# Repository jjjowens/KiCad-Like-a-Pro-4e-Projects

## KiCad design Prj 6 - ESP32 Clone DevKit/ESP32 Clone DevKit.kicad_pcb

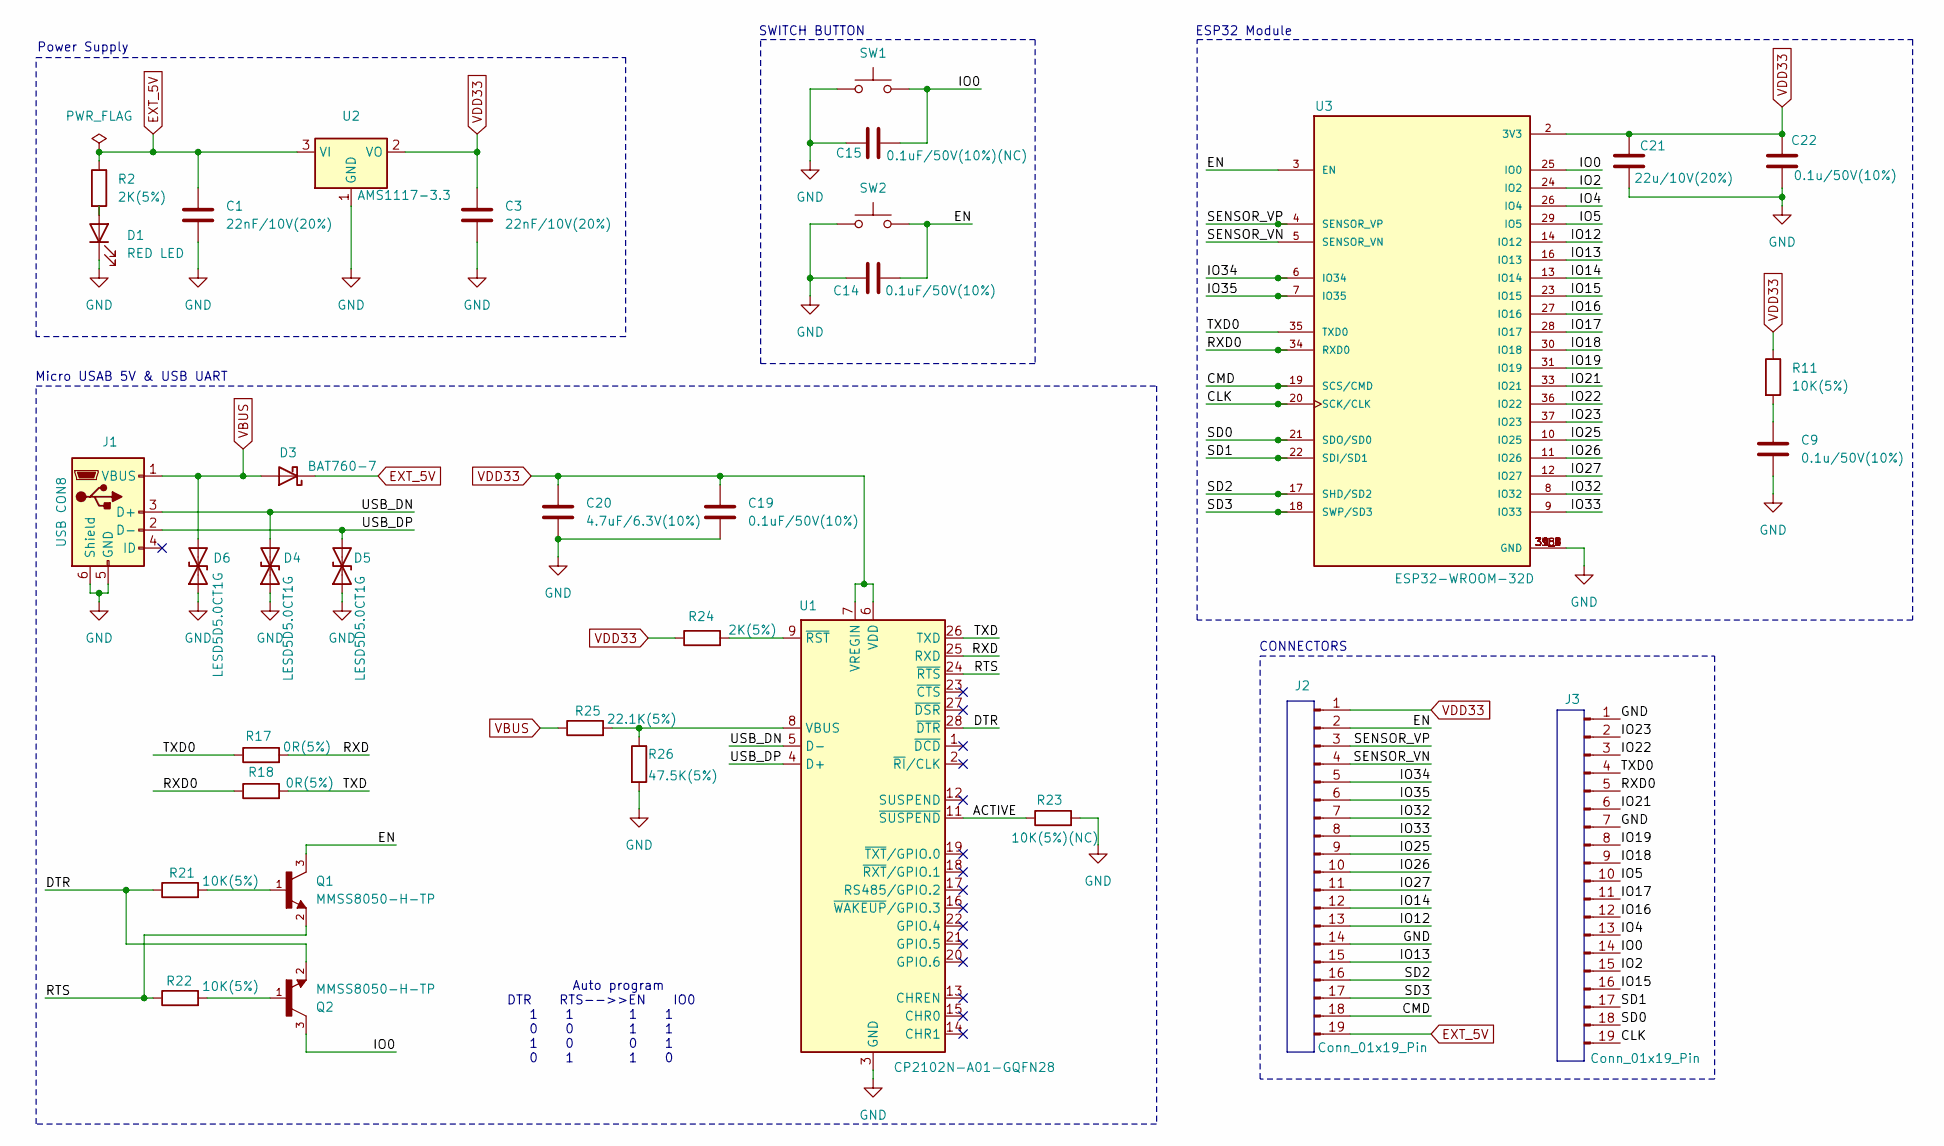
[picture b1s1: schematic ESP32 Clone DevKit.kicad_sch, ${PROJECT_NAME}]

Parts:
C1, C3: 22nF/10V(20%); C_0201_0603Metric
C9, C22: 0.1u/50V(10%); C_01005_0402Metric
C14, C19: 0.1uF/50V(10%); C_01005_0402Metric
C15: 0.1uF/50V(10%)(NC); C_01005_0402Metric
C20: 4.7uF/6.3V(10%); C_01005_0402Metric
C21: 22u/10V(20%); C_0201_0603Metric
D1: RED LED; LED_0603_1608Metric
D3: BAT760-7; D_SOD-323
D4, D5, D6: LESD5D5.0CT1G; D_SOD-523
J1: USB CON8; USB_Micro-AB_Molex_47590-0001
J2, J3: Conn_01x19_Pin; PinHeader_1x19_P2.54mm_Vertical
Q1, Q2: MMSS8050-H-TP; TRANS_MMSS8050-H-TP; PARTREV D
R2, R24: 2K(5%); R_01005_0402Metric_Pad0.57x0.30mm_HandSolder
R11, R21, R22: 10K(5%); R_01005_0402Metric_Pad0.57x0.30mm_HandSolder
R17, R18: 0R(5%); R_01005_0402Metric_Pad0.57x0.30mm_HandSolder
R23: 10K(5%)(NC); R_01005_0402Metric_Pad0.57x0.30mm_HandSolder
R25: 22.1K(5%); R_01005_0402Metric_Pad0.57x0.30mm_HandSolder
R26: 47.5K(5%); R_01005_0402Metric_Pad0.57x0.30mm_HandSolder
SW1, SW2: SW_Push; SW_SPST_B3S-1000
U1: CP2102N-A01-GQFN28; QFN-28-1EP_5x5mm_P0.5mm_EP3.35x3.35mm
U2: AMS1117-3.3; SOT-223-3_TabPin2
U3: ESP32-WROOM-32D; MODULE_ESP32-WROOM-32D; PARTREV 1.9

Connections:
/ACTIVE: R23.1, U1.11 (~SUSPEND)
/CLK: J3.19, U3.20 (SCK/CLK)
/CMD: J2.18, U3.19 (SCS/CMD)
/DTR: Q2.2, R21.1, U1.28 (~DTR)
/EN: C14.2, J2.2, Q1.3, SW2.2, U3.3 (EN); also elsewhere on the board
/IO0: C15.2, J3.14, Q2.3, SW1.2, U3.25 (IO0); also elsewhere on the board
/IO2: J3.15, U3.24 (IO2)
/IO4: J3.13, U3.26 (IO4)
/IO5: J3.10, U3.29 (IO5)
/IO12: J2.13, U3.14 (IO12)
/IO13: J2.15, U3.16 (IO13)
/IO14: J2.12, U3.13 (IO14)
/IO15: J3.16, U3.23 (IO15)
/IO16: J3.12, U3.27 (IO16)
/IO17: J3.11, U3.28 (IO17)
/IO18: J3.9, U3.30 (IO18)
/IO19: J3.8, U3.31 (IO19)
/IO21: J3.6, U3.33 (IO21)
/IO22: J3.3, U3.36 (IO22)
/IO23: J3.2, U3.37 (IO23)
/IO25: J2.9, U3.10 (IO25)
/IO26: J2.10, U3.11 (IO26)
/IO27: J2.11, U3.12 (IO27)
/IO32: J2.7, U3.8 (IO32)
/IO33: J2.8, U3.9 (IO33)
/IO34: J2.5, U3.6 (IO34)
/IO35: J2.6, U3.7 (IO35)
/RTS: Q1.2, R22.1, U1.24 (~RTS)
/RXD: R17.2, U1.25 (RXD)
/RXD0: J3.5, R18.1, U3.34 (RXD0)
/SD0: J3.18, U3.21 (SDO/SD0)
/SD1: J3.17, U3.22 (SDI/SD1)
/SD2: J2.16, U3.17 (SHD/SD2)
/SD3: J2.17, U3.18 (SWP/SD3)
/SENSOR_VN: J2.4, U3.5 (SENSOR_VN)
/SENSOR_VP: J2.3, U3.4 (SENSOR_VP)
/TXD: R18.2, U1.26 (TXD)
/TXD0: J3.4, R17.1, U3.35 (TXD0)
/USB_DN: D4.2 (A2), J1.3 (D+), U1.5 (D-)
/USB_DP: D5.2 (A2), J1.2 (D-), U1.4 (D+)
EXT_5V: C1.1, D3.1 (K), J2.19, R2.1, U2.3 (VI)
GND: C1.2, C3.2, C9.2, C14.1, C15.1, C19.2, C20.2, C21.2, C22.2, D1.1 (K), D4.1 (A1), D5.1 (A1), D6.1 (A1), J1.5 (GND), J1.6 (Shield), J2.14, J3.1, J3.7, R23.2, R26.2, SW1.1, SW2.1, U1.3 (GND), U1.29 (GND), U2.1 (GND), U3.1 (GND), U3.15 (GND), U3.38 (GND), U3.39_1 (GND), U3.39_2 (GND), U3.39_3 (GND), U3.39_4 (GND), U3.39_5 (GND), U3.39_6 (GND), U3.39_7 (GND), U3.39_8 (GND), U3.39_9 (GND); also elsewhere on the board
unnamed: C9.1, R11.2
unnamed: D1.2 (A), R2.2
unnamed: Q1.1, R21.2
unnamed: Q2.1, R22.2
unnamed: R25.2, R26.1, U1.8 (VBUS)
unnamed: R24.2, U1.9 (~RST)
VBUS: D3.2 (A), D6.2 (A2), J1.1 (VBUS), R25.1
VDD33: C3.1, C19.1, C20.1, C21.1, C22.1, J2.1, R11.1, R24.1, U1.6 (VDD), U1.7 (VREGIN), U2.2 (VO), U3.2 (3V3)

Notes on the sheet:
CONNECTORS
SWITCH BUTTON
ESP32 Module
Micro USAB 5V & USB UART
Auto program DTR RTS-->>EN IO0 1 1 1 1 0 0 1 1 1 0 0 1 0 1 1 0
Power Supply

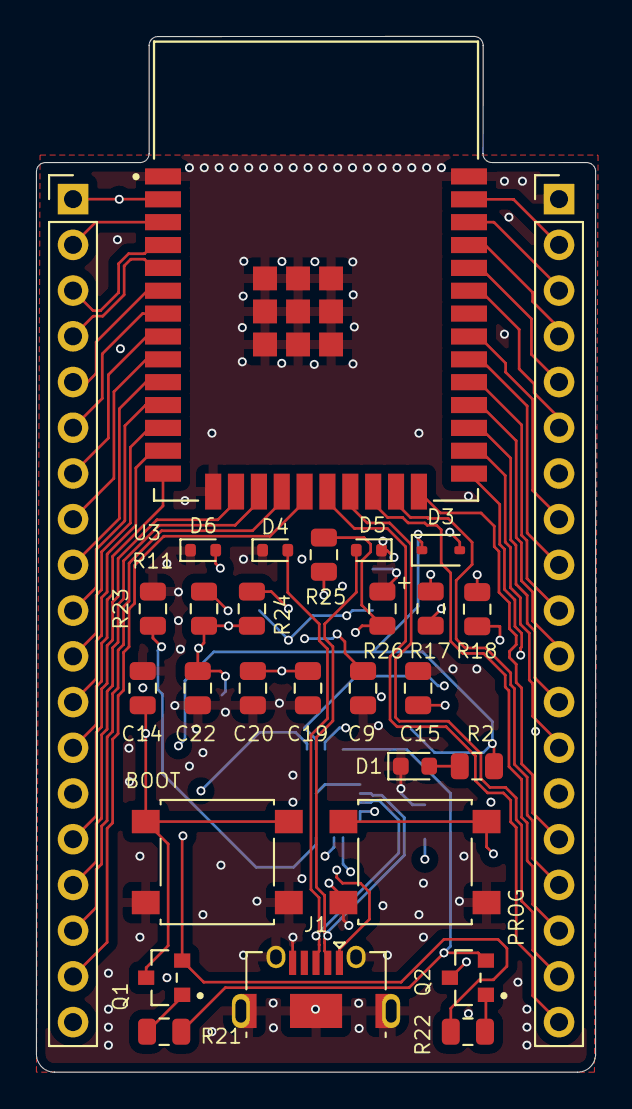
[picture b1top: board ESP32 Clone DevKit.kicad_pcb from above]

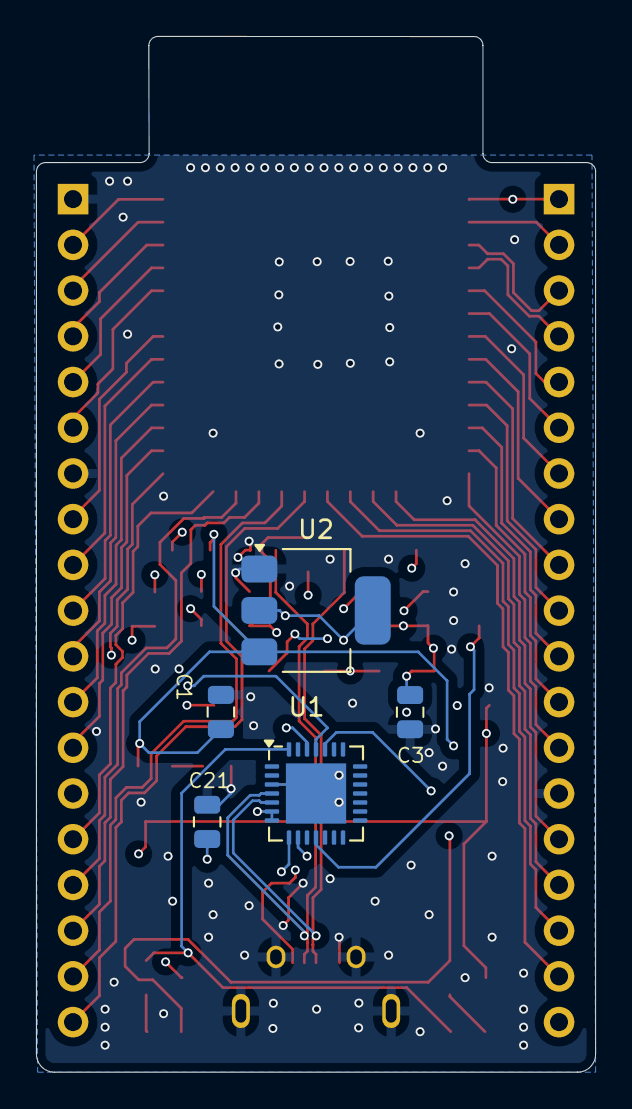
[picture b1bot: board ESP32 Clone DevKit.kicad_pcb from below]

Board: 4 copper layers, 31.1 x 57.5 mm, 34 parts (5 on the bottom side), 50 nets.

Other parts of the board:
BOOT: SW_Push; SW_SPST_B3S-1000
PROG: SW_Push; SW_SPST_B3S-1000

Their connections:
/EN: BOOT.2; also elsewhere on the board
/IO0: PROG.2; also elsewhere on the board
GND: BOOT.1, PROG.1; also elsewhere on the board

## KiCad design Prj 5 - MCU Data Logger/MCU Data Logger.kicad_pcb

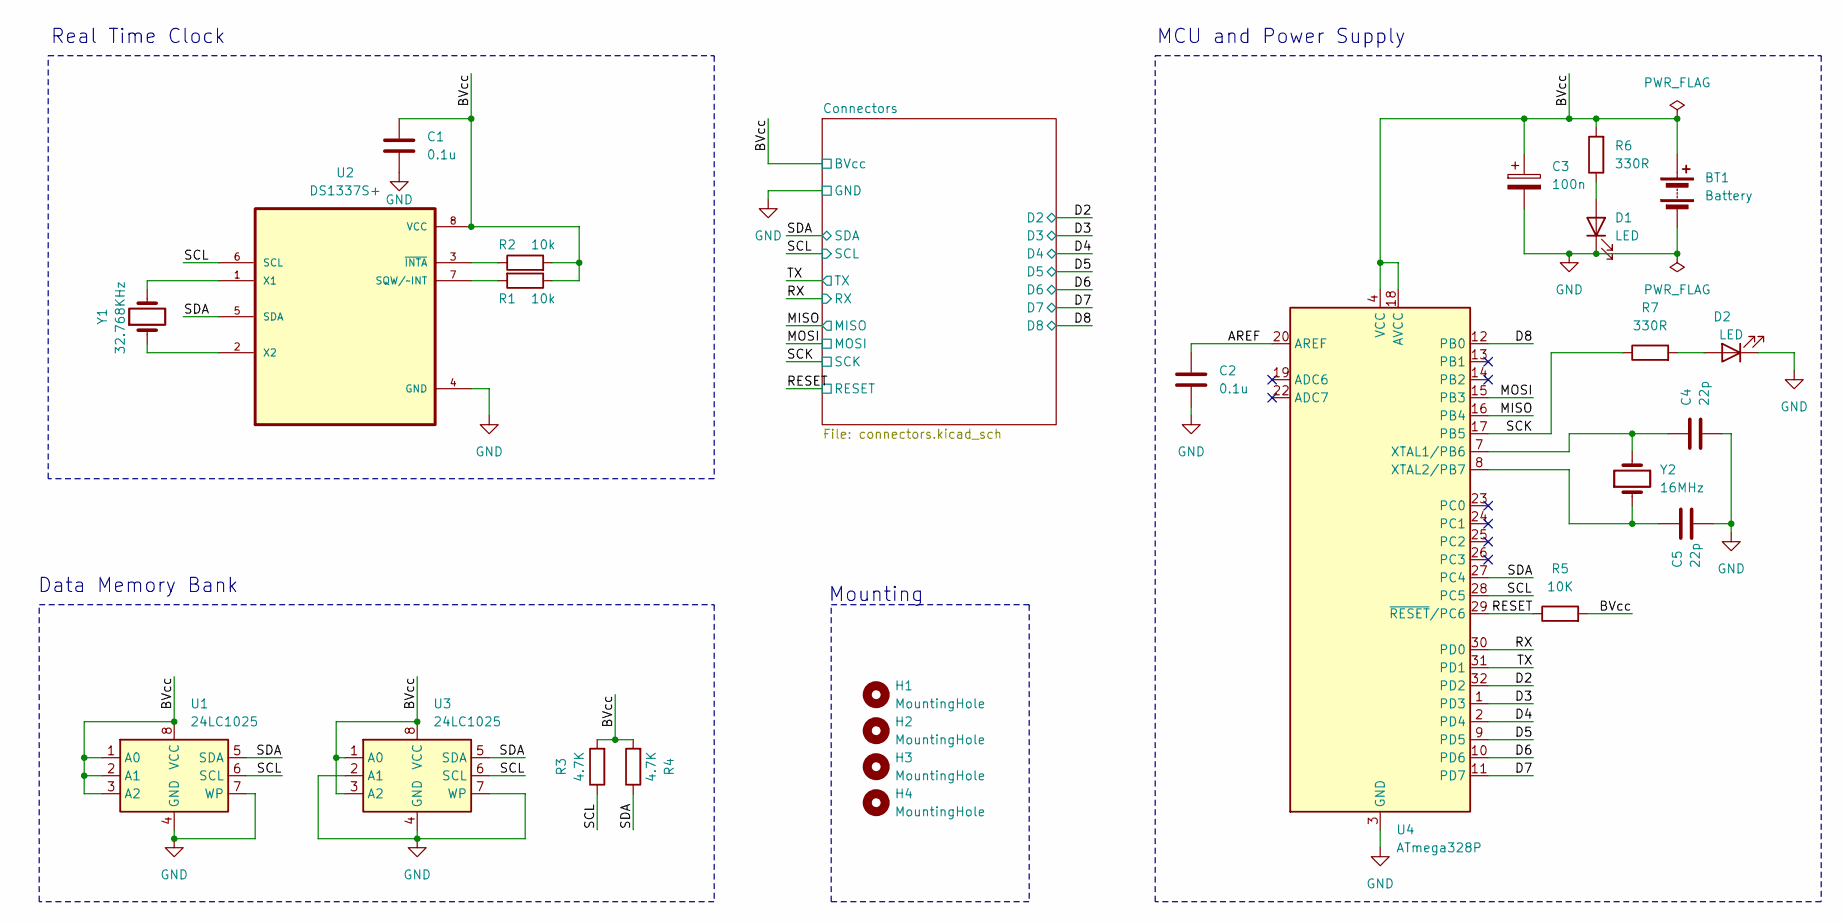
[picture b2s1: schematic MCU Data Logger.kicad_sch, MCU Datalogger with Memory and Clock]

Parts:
BT1: Battery; PinHeader_1x02_P2.54mm_Vertical
C1, C2: 0.1u; C_0805_2012Metric
C3: 100n; C_0805_2012Metric
C4, C5: 22p; C_0805_2012Metric
D1, D2: LED; LED_0805_2012Metric
H1, H2, H3, H4: MountingHole; MountingHole_2.1mm
R1, R2: 10k; R_0805_2012Metric
R3, R4: 4.7K; R_0805_2012Metric
R5: 10K; R_0805_2012Metric
R6, R7: 330R; R_0805_2012Metric
U1, U3: 24LC1025; SOIC-8_5.23x5.23mm_P1.27mm
U2: DS1337S+; SOIC127P600X175-8N
U4: ATmega328P; TQFP-32_7x7mm_P0.8mm
Y1: 32.768KHz; Crystal_SMD_5032-2Pin_5.0x3.2mm
Y2: 16MHz; Crystal_SMD_5032-2Pin_5.0x3.2mm

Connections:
/AREF: C2.1, U4.20 (AREF)
/BVcc: BT1.1 (+), C1.1, C3.1, R1.2, R2.1, R3.2, R4.2, R5.2, R6.2, U1.1 (A0), U1.2 (A1), U1.3 (A2), U1.8 (VCC), U2.8 (VCC), U3.1 (A0), U3.3 (A2), U3.8 (VCC), U4.4 (VCC), U4.6 (VCC), U4.18 (AVCC); also elsewhere on the board
/D2: U4.32 (PD2); also elsewhere on the board
/D3: U4.1 (PD3); also elsewhere on the board
/D4: U4.2 (PD4); also elsewhere on the board
/D5: U4.9 (PD5); also elsewhere on the board
/D6: U4.10 (PD6); also elsewhere on the board
/D7: U4.11 (PD7); also elsewhere on the board
/D8: U4.12 (PB0); also elsewhere on the board
/MISO: U4.16 (PB4); also elsewhere on the board
/MOSI: U4.15 (PB3); also elsewhere on the board
/RESET: R5.1, U4.29 (~RESET/PC6); also elsewhere on the board
/RX: U4.30 (PD0); also elsewhere on the board
/SCK: R7.1, U4.17 (PB5); also elsewhere on the board
/SCL: R3.1, U1.6 (SCL), U2.6 (SCL), U3.6 (SCL), U4.28 (PC5); also elsewhere on the board
/SDA: R4.1, U1.5 (SDA), U2.5 (SDA), U3.5 (SDA), U4.27 (PC4); also elsewhere on the board
/TX: U4.31 (PD1); also elsewhere on the board
GND: BT1.2 (-), C1.2, C2.2, C3.2, C4.2, C5.2, D1.1 (K), D2.1 (K), U1.4 (GND), U1.7 (WP), U2.4 (GND), U3.2 (A1), U3.4 (GND), U3.7 (WP), U4.3 (GND), U4.5 (GND), U4.21 (GND); also elsewhere on the board
unnamed: D1.2 (A), R6.1
unnamed: D2.2 (A), R7.2
unnamed: R2.2, U2.7 (SQW/~INT)
unnamed: U2.1 (X1), Y1.2
unnamed: U2.2 (X2), Y1.1
unnamed: R1.1, U2.3 (~INTA)
unnamed: C4.1, U4.7 (XTAL1/PB6), Y2.2
unnamed: C5.1, U4.8 (XTAL2/PB7), Y2.1

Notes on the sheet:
MCU and Power Supply
Mounting
Real Time Clock
Data Memory Bank

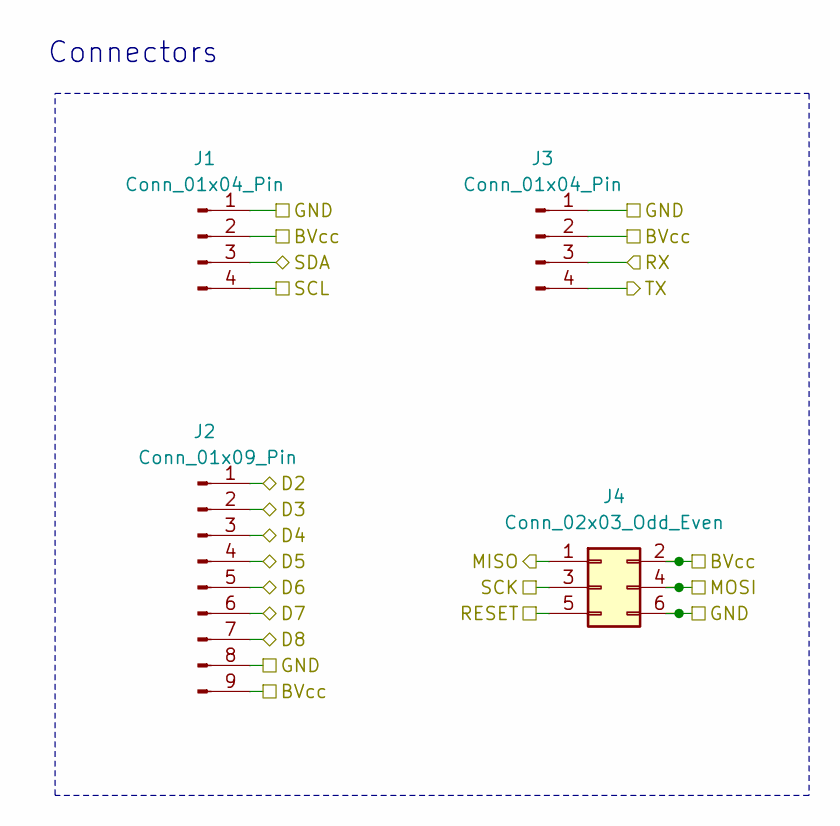
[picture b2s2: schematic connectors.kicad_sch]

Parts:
J1, J3: Conn_01x04_Pin; PinHeader_1x04_P2.54mm_Vertical
J2: Conn_01x09_Pin; PinHeader_1x09_P2.54mm_Vertical
J4: Conn_02x03_Odd_Even; PinHeader_2x03_P2.54mm_Vertical

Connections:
/BVcc: J1.2, J2.9, J3.2, J4.2; also elsewhere on the board
/D2: J2.1; also elsewhere on the board
/D3: J2.2; also elsewhere on the board
/D4: J2.3; also elsewhere on the board
/D5: J2.4; also elsewhere on the board
/D6: J2.5; also elsewhere on the board
/D7: J2.6; also elsewhere on the board
/D8: J2.7; also elsewhere on the board
/MISO: J4.1; also elsewhere on the board
/MOSI: J4.4; also elsewhere on the board
/RESET: J4.5; also elsewhere on the board
/RX: J3.3; also elsewhere on the board
/SCK: J4.3; also elsewhere on the board
/SCL: J1.4; also elsewhere on the board
/SDA: J1.3; also elsewhere on the board
/TX: J3.4; also elsewhere on the board
GND: J1.1, J2.8, J3.1, J4.6; also elsewhere on the board

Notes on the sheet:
Connectors

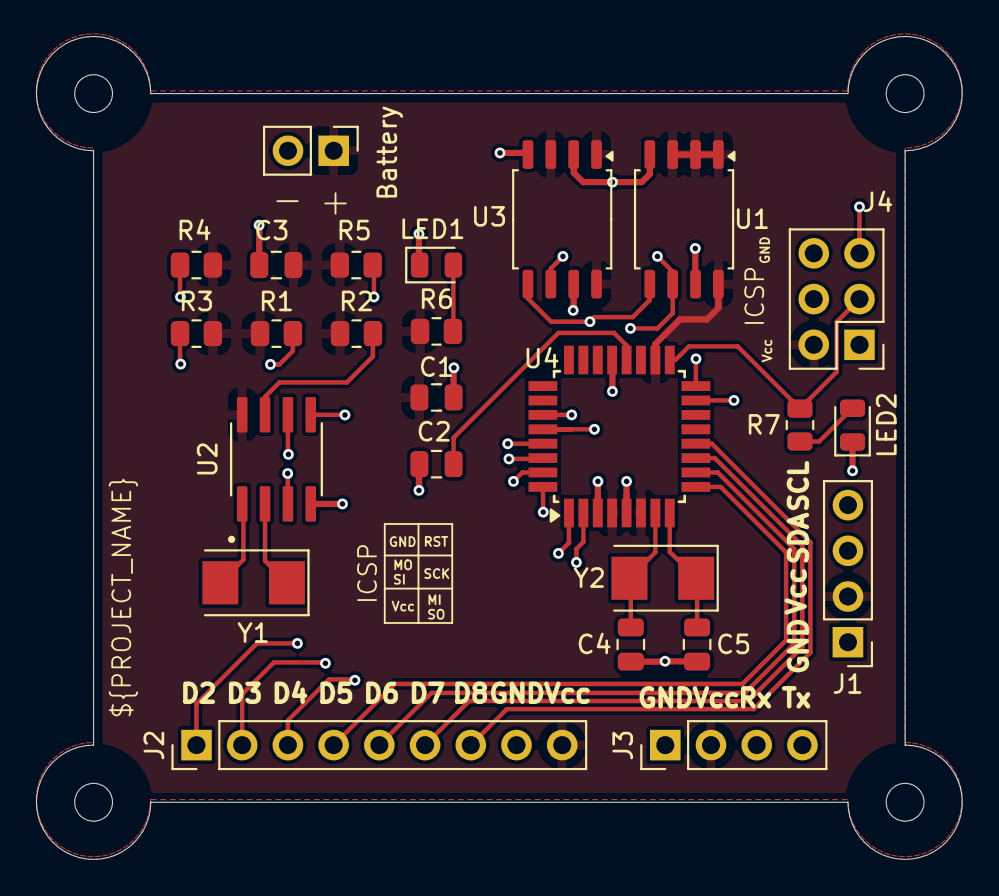
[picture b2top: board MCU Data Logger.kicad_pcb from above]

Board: 4 copper layers, 51.4 x 45.7 mm, 29 parts (0 on the bottom side), 26 nets.

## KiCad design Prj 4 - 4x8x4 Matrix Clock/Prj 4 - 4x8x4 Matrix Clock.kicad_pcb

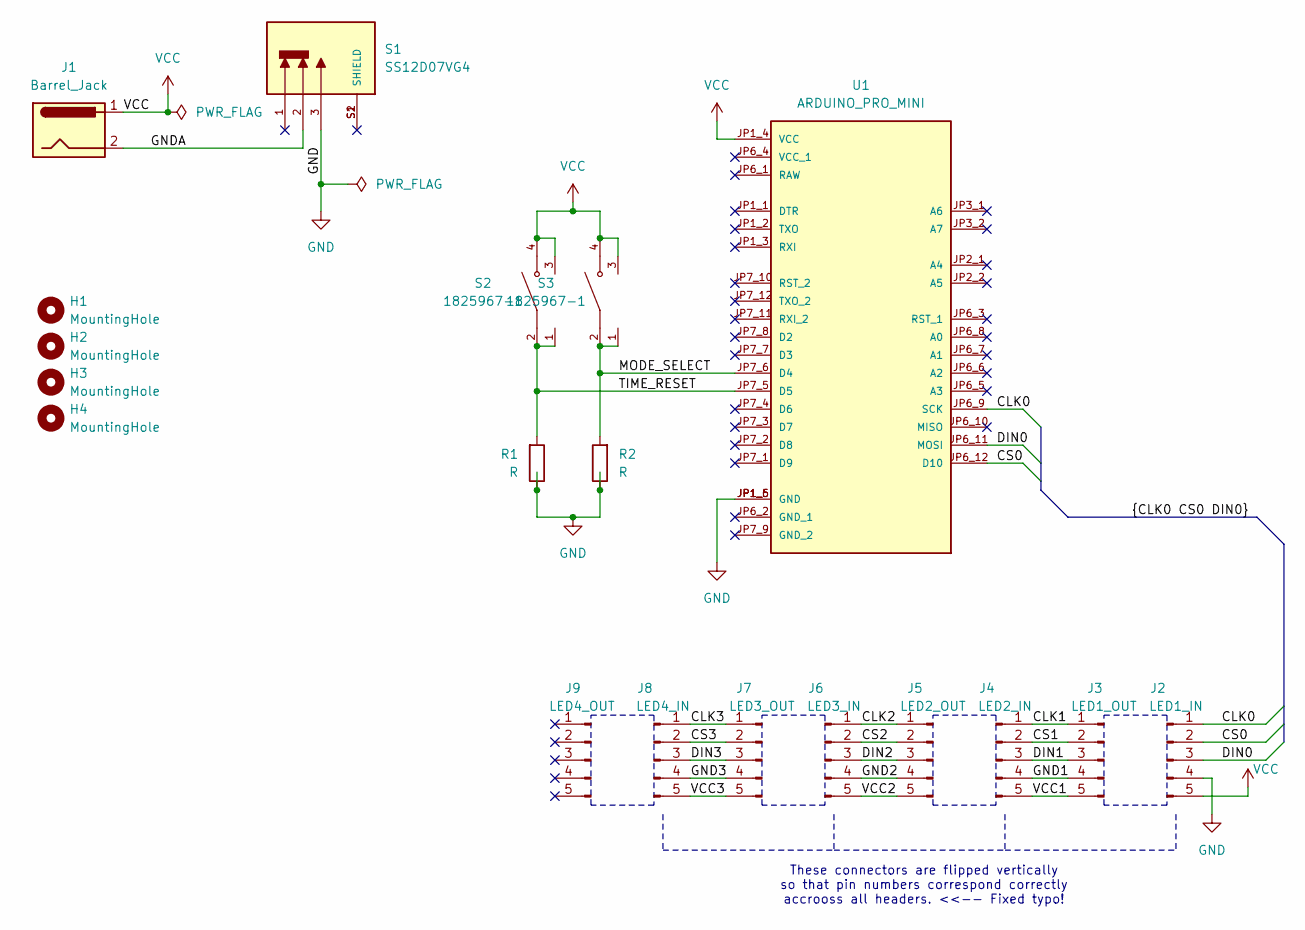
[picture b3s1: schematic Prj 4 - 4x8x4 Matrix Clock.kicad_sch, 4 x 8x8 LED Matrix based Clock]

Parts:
H1, H2, H3, H4: MountingHole; MountingHole_2.5mm
J1: Barrel_Jack; BarrelJack_Horizontal
J2, J3, J4, J5, J6, J7, J8, J9: Conn_01x05_Pin; PinHeader_1x05_P2.54mm_Vertical
R1, R2: R; R_Axial_DIN0309_L9.0mm_D3.2mm_P12.70mm_Horizontal
S1: SS12D07VG4; SW_SS12D07VG4; PARTREV 1
S2, S3: 1825967-1; SW_1825967-1; PARTREV E
U1: ARDUINO_PRO_MINI; MODULE_ARDUINO_PRO_MINI; PARTREV N/A

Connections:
/CLK0: J2.1, U1.JP6_9 (SCK)
/CLK1: J3.1, J4.1
/CLK2: J5.1, J6.1
/CLK3: J7.1, J8.1
/CS0: J2.2, U1.JP6_12 (D10)
/CS1: J3.2, J4.2
/CS2: J5.2, J6.2
/CS3: J7.2, J8.2
/DIN0: J2.3, U1.JP6_11 (MOSI)
/DIN1: J3.3, J4.3
/DIN2: J5.3, J6.3
/DIN3: J7.3, J8.3
/GND1: J3.4, J4.4
/GND2: J5.4, J6.4
/GND3: J7.4, J8.4
/GNDA: J1.2, S1.2
/MODE_SELECT: R2.2, S3.1, S3.2, U1.JP7_6 (D4)
/TIME_RESET: R1.2, S2.1, S2.2, U1.JP7_5 (D5)
/VCC1: J3.5, J4.5
/VCC2: J5.5, J6.5
/VCC3: J7.5, J8.5
GND: J2.4, R1.1, R2.1, S1.3, U1.JP1_5 (GND), U1.JP1_6 (GND)
VCC: J1.1, J2.5, S2.3, S2.4, S3.3, S3.4, U1.JP1_4 (VCC)

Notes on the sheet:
These connectors are flipped vertically so that pin numbers correspond correctly accrooss all headers. <<-- Fixed typo!

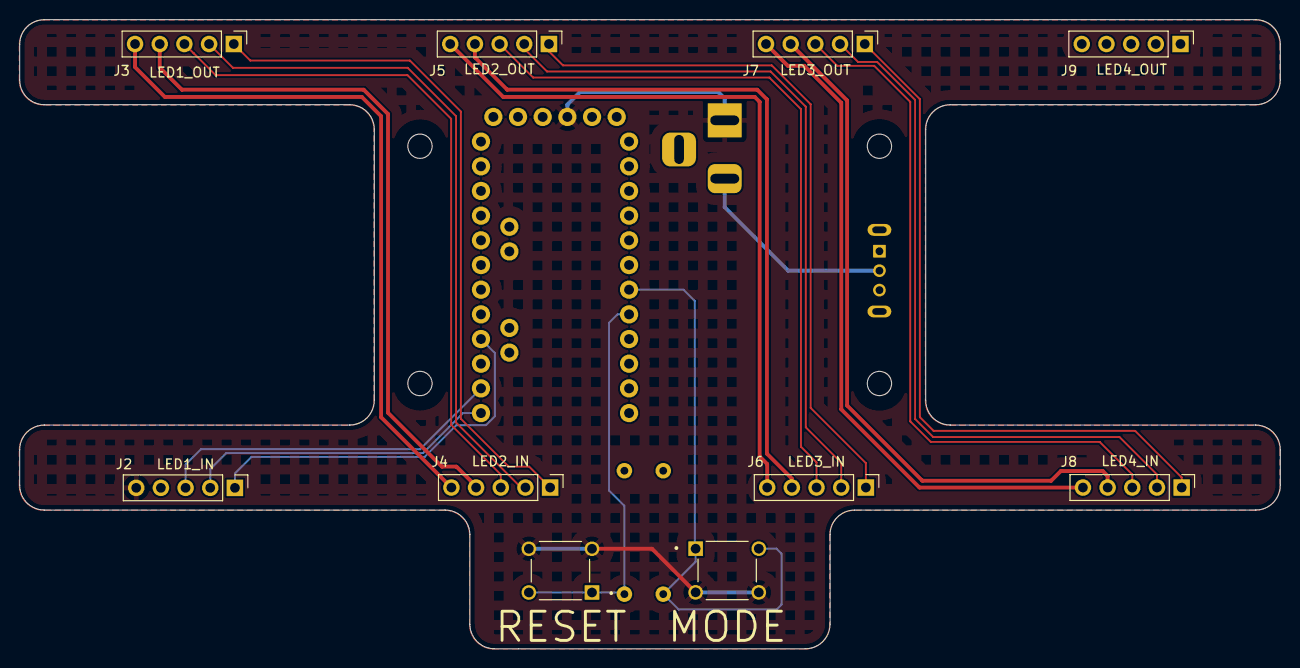
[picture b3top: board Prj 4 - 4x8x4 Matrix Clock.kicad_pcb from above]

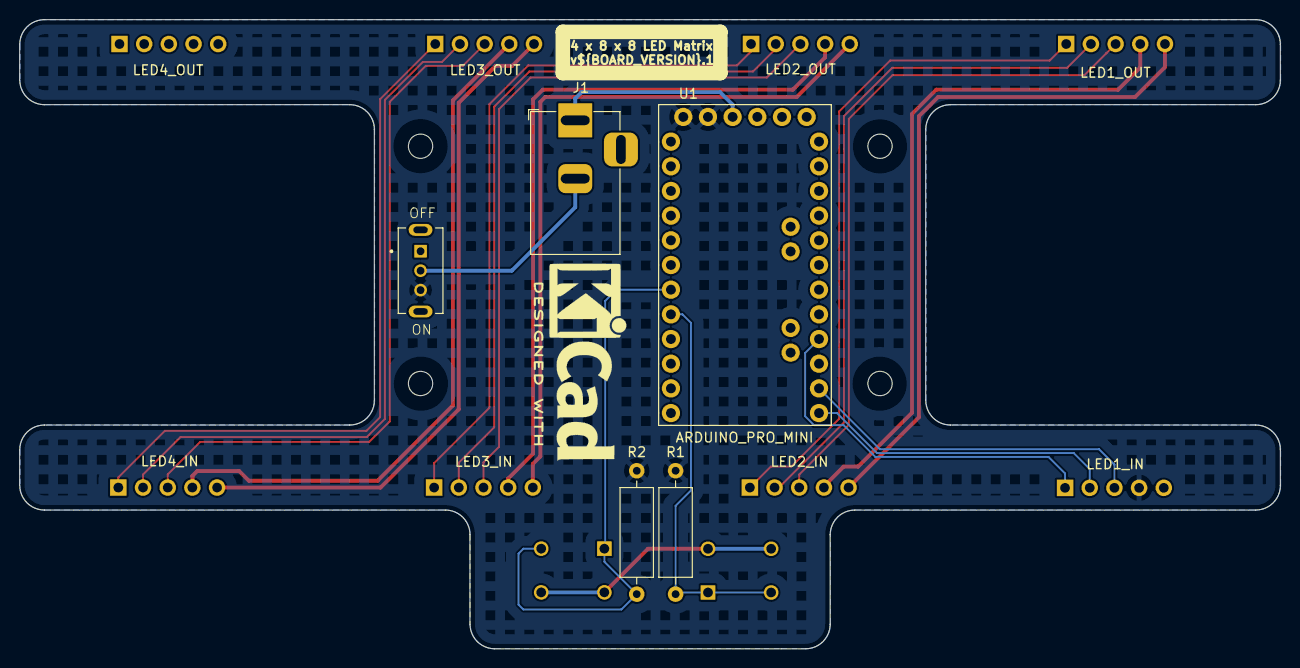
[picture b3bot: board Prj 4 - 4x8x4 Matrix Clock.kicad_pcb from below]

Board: 2 copper layers, 129.8 x 64.8 mm, 19 parts (5 on the bottom side), 23 nets.

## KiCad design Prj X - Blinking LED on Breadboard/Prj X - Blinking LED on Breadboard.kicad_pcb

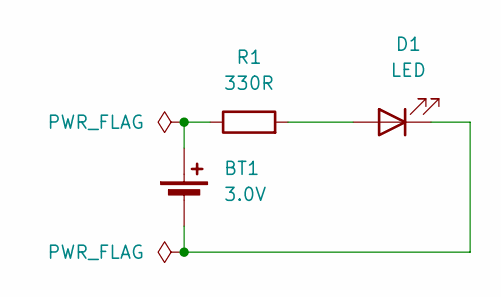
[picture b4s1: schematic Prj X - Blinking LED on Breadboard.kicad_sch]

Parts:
BT1: 3.0V; BatteryHolder_Keystone_2468_2xAAA
D1: LED; LED_D5.0mm_Clear
R1: 330R; R_Axial_DIN0414_L11.9mm_D4.5mm_P20.32mm_Horizontal

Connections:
unnamed: BT1.1 (+), R1.1
unnamed: BT1.2 (-), D1.1 (K)
unnamed: D1.2 (A), R1.2

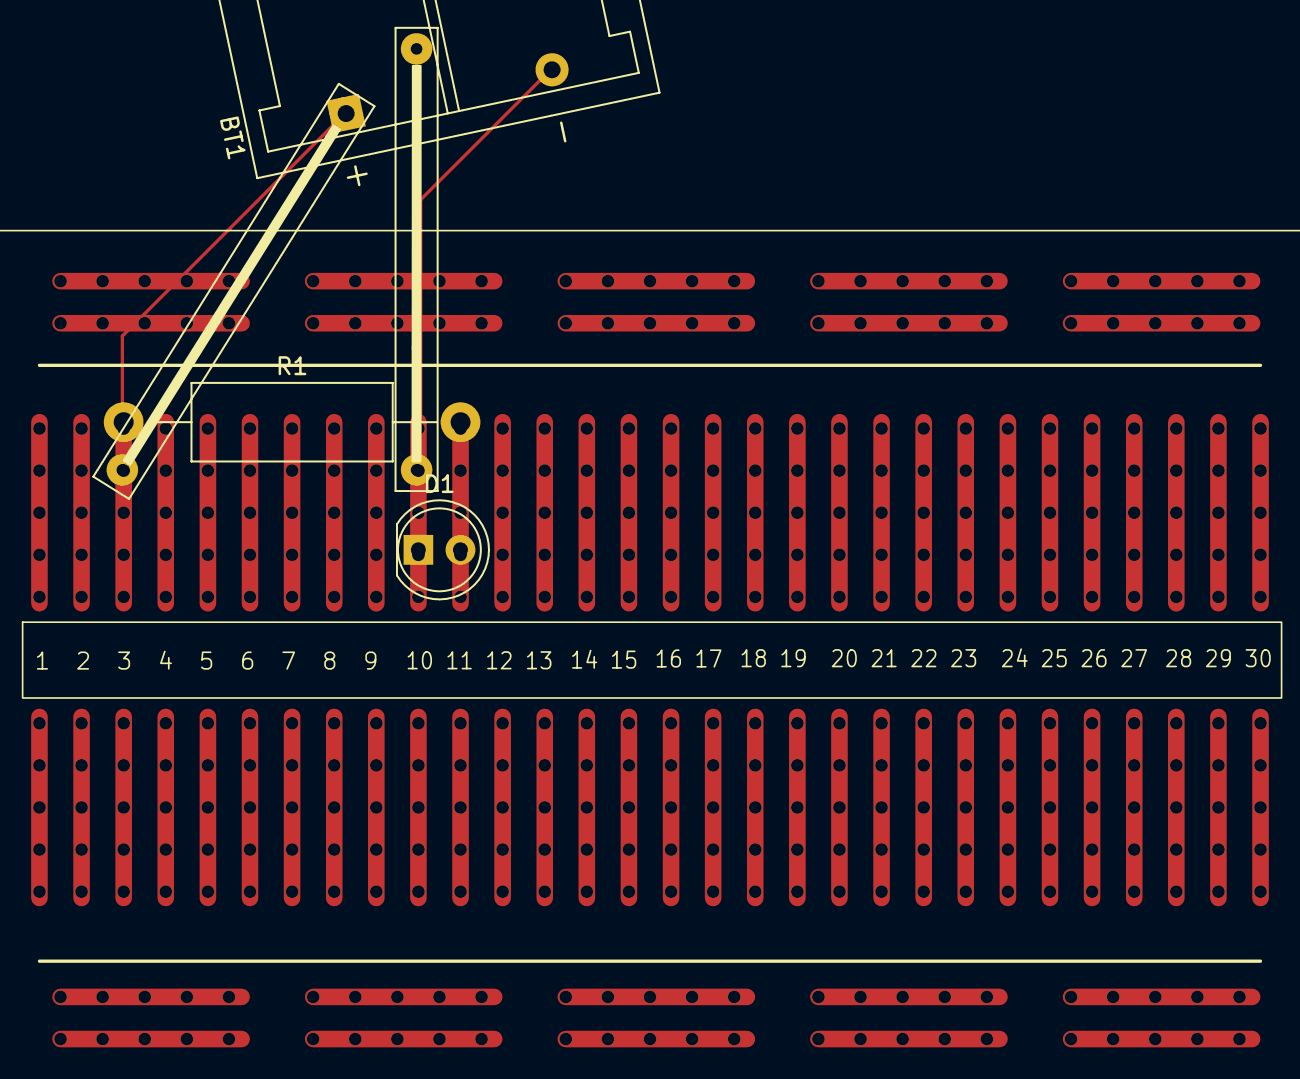
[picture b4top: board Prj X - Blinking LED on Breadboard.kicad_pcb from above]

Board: 2 copper layers, 3 parts (0 on the bottom side), 3 nets.

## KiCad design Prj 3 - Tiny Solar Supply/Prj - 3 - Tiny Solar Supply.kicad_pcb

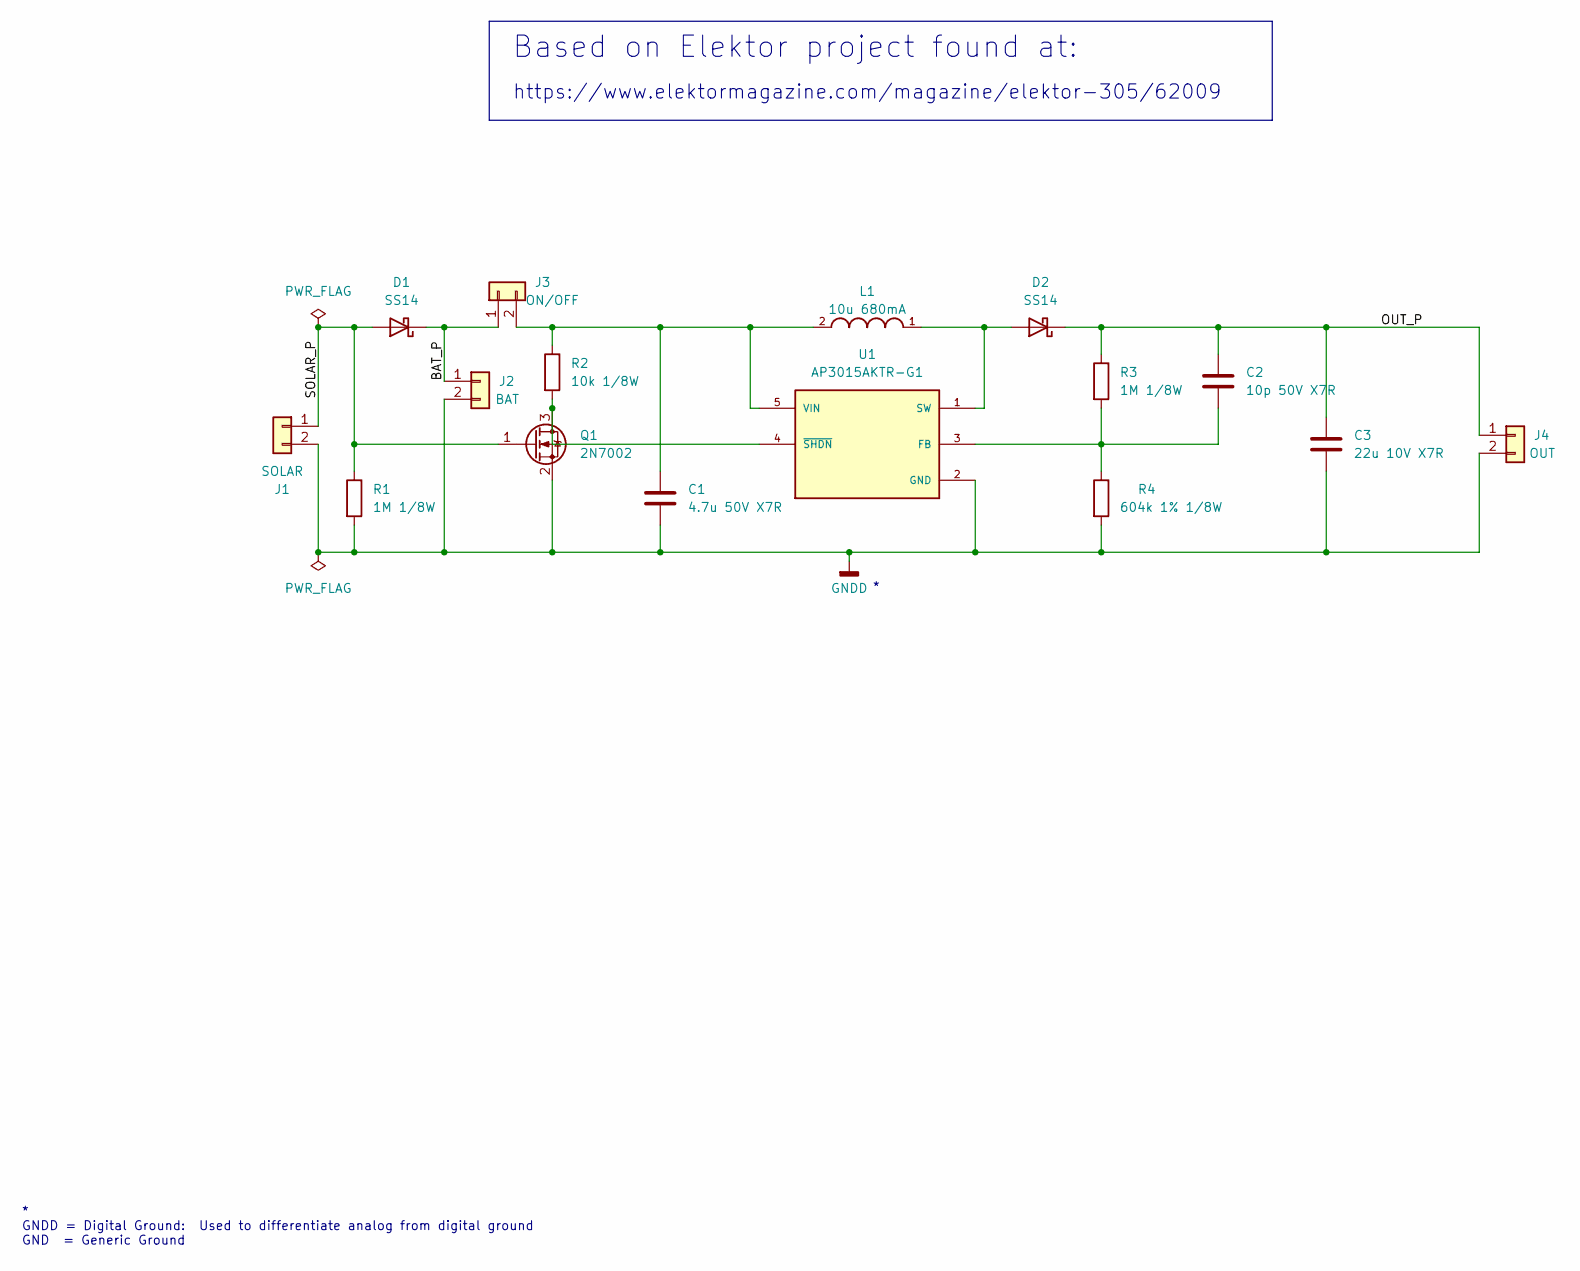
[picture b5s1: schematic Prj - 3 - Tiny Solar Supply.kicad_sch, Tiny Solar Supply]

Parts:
C1: 4.7u 50V X7R; C_0805_2012Metric
C2: 10p 50V X7R; C_0805_2012Metric
C3: 22u 10V X7R; C_1206_3216Metric
D1, D2: SS14; D_SMA
J1: Conn_01x02_Pin; PinHeader_1x02_P2.00mm_Horizontal
J2, J4: Conn_01x02_Pin; PinHeader_1x02_P2.54mm_Horizontal
J3: Conn_01x02_Pin; SW_DIP_SPSTx01_Slide_9.78x4.72mm_W8.61mm_P2.54mm
L1: 10u 680mA; INDC2518X200N
Q1: 2N7002; SOT-23
R1, R3: 1M 1/8W; R_0805_2012Metric
R2: 10k 1/8W; R_0805_2012Metric
R4: 604k 1% 1/8W; R_0805_2012Metric
U1: AP3015AKTR-G1; SOT95P280X145-5N; PARTREV 1.4

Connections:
/BAT_P: D1.1 (K), J2.1, J3.1
/OUT_P: C2.1, C3.1, D2.1 (K), J4.1, R3.1
/SOLAR_P: D1.2 (A), J1.1, Q1.1 (G), R1.1
GNDD: C1.2, C3.2, J1.2, J2.2, J4.2, Q1.2 (S), R1.2, R4.2, U1.2 (GND)
unnamed: D2.2 (A), L1.1, U1.1 (SW)
unnamed: C1.1, J3.2, L1.2, R2.1, U1.5 (VIN)
unnamed: Q1.3 (D), R2.2, U1.4 (~SHDN)
unnamed: C2.2, R3.2, R4.1, U1.3 (FB)

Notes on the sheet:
https://www.elektormagazine.com/magazine/elektor-305/62009
Based on Elektor project found at:
* GNDD = Digital Ground: Used to differentiate analog from digital ground GND = Generic Ground

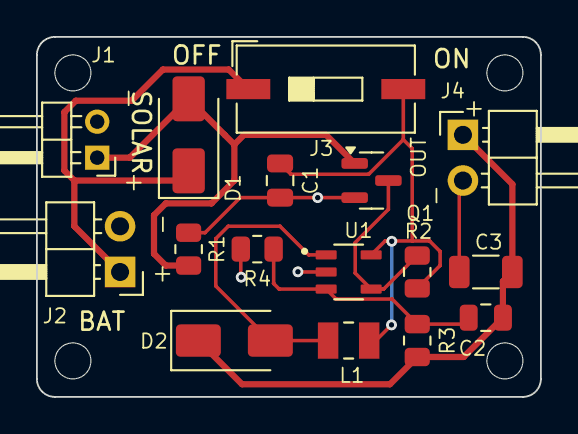
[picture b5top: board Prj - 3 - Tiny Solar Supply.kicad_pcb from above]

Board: 2 copper layers, 28.0 x 20.0 mm, 16 parts (0 on the bottom side), 8 nets.

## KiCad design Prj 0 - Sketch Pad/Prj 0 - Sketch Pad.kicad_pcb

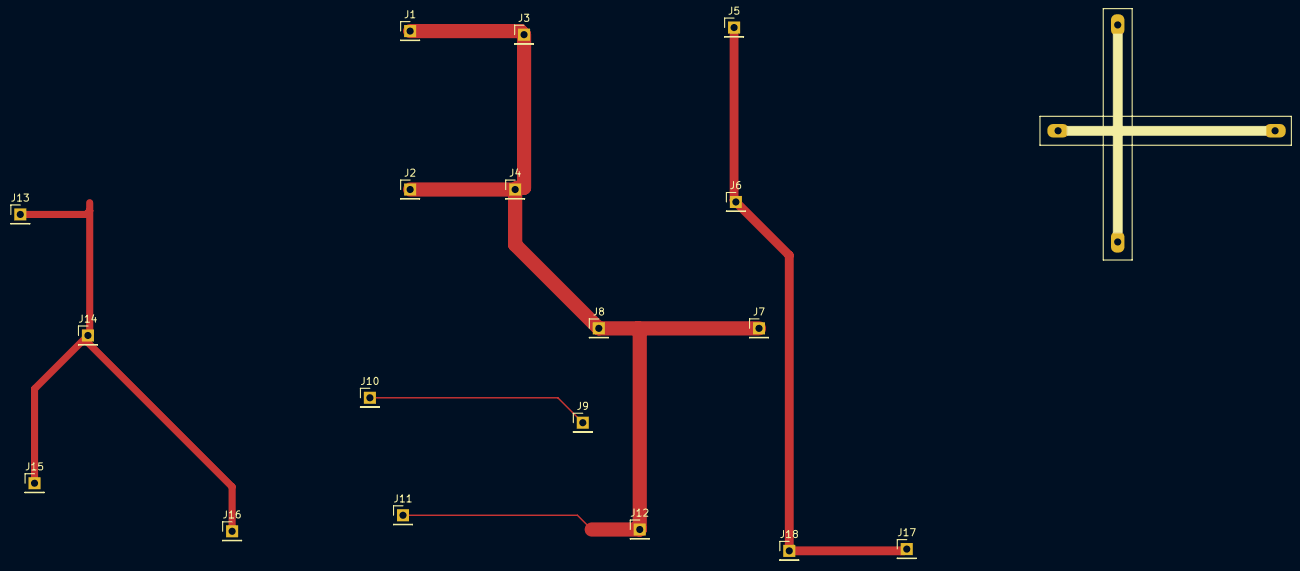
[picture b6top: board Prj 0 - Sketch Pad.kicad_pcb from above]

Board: 2 copper layers, 18 parts (0 on the bottom side), 4 nets.

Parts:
J1, J2, J3, J4, J5, J6, J7, J8, J9, J10, J11, J12, J13, J14, J15, J16, J17, J18: Conn_01x01_Socket; PinHeader_1x01_P2.54mm_Vertical

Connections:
/net_2: J5.1, J6.1, J17.1, J18.1
/net_3: J13.1, J14.1, J15.1, J16.1
Global_1: J1.1, J2.1, J3.1, J4.1, J7.1, J8.1, J11.1, J12.1
Global_2: J9.1, J10.1

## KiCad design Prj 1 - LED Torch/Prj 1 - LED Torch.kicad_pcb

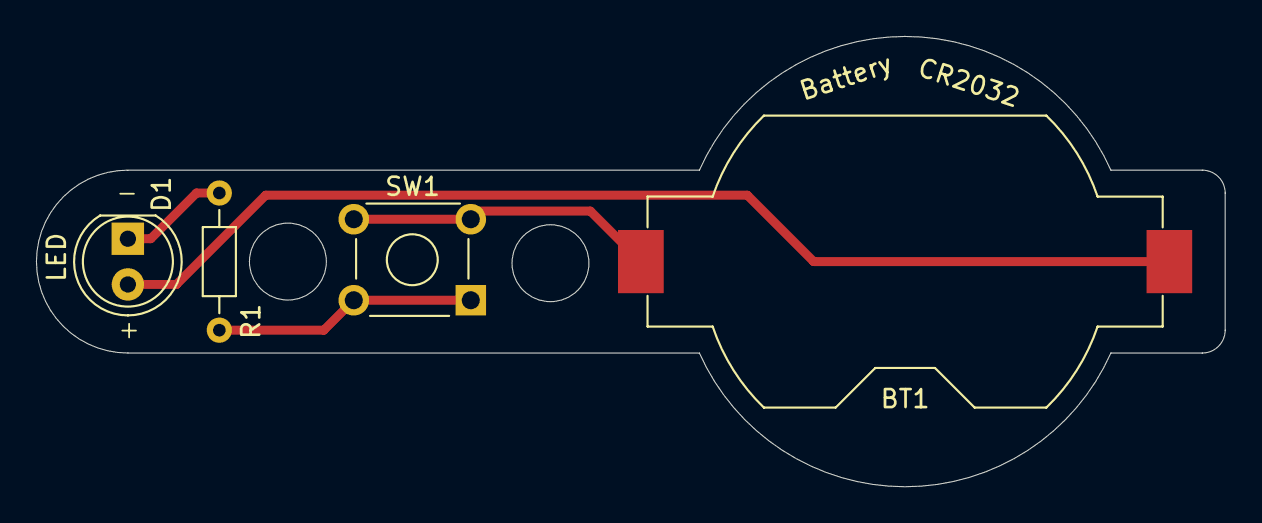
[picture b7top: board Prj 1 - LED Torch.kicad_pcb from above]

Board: 2 copper layers, 66.0 x 25.0 mm, 5 parts (1 on the bottom side), 4 nets.

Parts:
BT1: Battery; BatteryHolder_Keystone_1058_1x2032
D1: LED; LED_D5.0mm
R1: R; R_Axial_DIN0204_L3.6mm_D1.6mm_P7.62mm_Horizontal
REF1: KiCad-Logo2_5mm_SilkScreen
SW1: SW_DPST_x2; SW_TH_Tactile_Omron_B3F-10xx

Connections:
/BATT_pos: BT1.1 (+), SW1.2 (B)
/LED_anode: D1.1 (K), R1.1
/LED_cathode: BT1.2 (-), D1.2 (A)
unnamed: R1.2, SW1.1 (A)
